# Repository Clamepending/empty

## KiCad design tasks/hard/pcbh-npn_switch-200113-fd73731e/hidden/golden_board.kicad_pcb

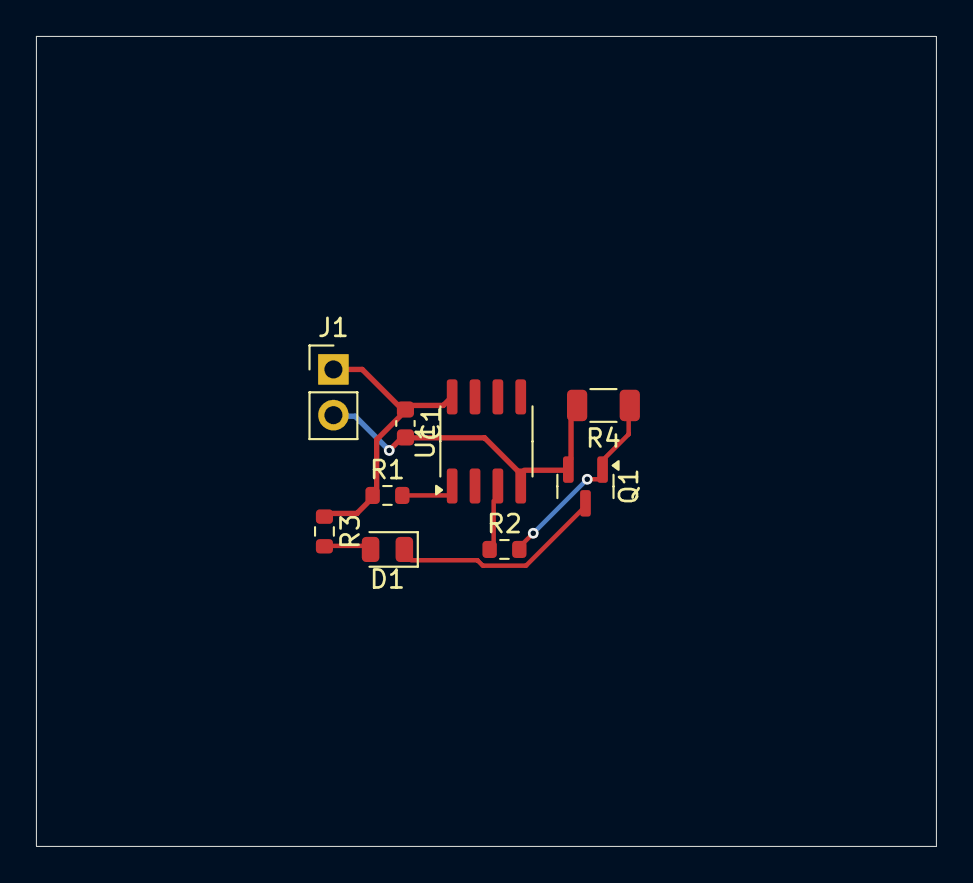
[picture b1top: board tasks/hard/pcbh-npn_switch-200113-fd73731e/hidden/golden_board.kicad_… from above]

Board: 2 copper layers, 50.0 x 45.0 mm, 9 parts (0 on the bottom side), 7 nets.

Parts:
C1: 100n; C_0603_1608Metric
D1: LED_0805_2012Metric
J1: PinHeader_1x02_P2.54mm_Vertical
Q1: SOT-23
R1: 24k; R_0603_1608Metric
R2: 1.1k; R_0603_1608Metric
R3: 51; R_0603_1608Metric
R4: 75k; R_1206_3216Metric
U1: SOIC-8_3.9x4.9mm_P1.27mm

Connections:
+3V3: C1.1, J1.1, R1.1, R3.1, U1.8
BASE: Q1.1, R2.2, R4.1
CTRL: R2.1, U1.3
GND: C1.2, J1.2, Q1.2, R4.2, U1.4
LED_A: D1.2, R3.2
NRST: R1.2, U1.1
SW: D1.1, Q1.3

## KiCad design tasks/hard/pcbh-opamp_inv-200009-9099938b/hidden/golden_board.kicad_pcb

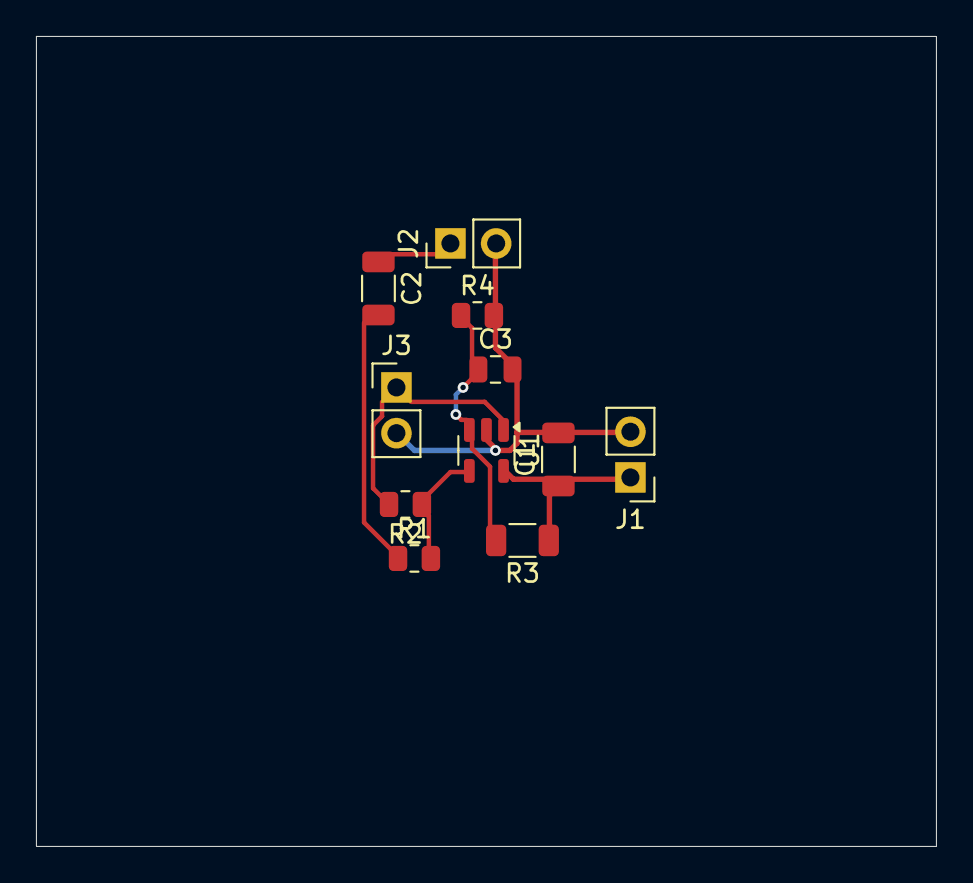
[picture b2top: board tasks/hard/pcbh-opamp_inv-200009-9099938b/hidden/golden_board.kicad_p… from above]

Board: 2 copper layers, 50.0 x 45.0 mm, 11 parts (0 on the bottom side), 7 nets.

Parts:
C1: 100n; C_1206_3216Metric
C2: 330n; C_1206_3216Metric
C3: 1u; C_0805_2012Metric
J1, J2, J3: PinHeader_1x02_P2.54mm_Vertical
R1, R2: 8.45k; R_0805_2012Metric
R3: 24k; R_1206_3216Metric
R4: 24k; R_0805_2012Metric
U1: SOT-23-5

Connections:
GND: C1.2, C3.2, J1.2, J2.2, J3.2, R4.2, U1.2
IN: C2.1, J2.1
IN_AC: C2.2, R1.1
OUT: J3.1, R2.2, U1.1
SUM: R1.2, R2.1, U1.4
VCC: C1.1, J1.1, R3.1, U1.5
VMID: C3.1, R3.2, R4.1, U1.3
